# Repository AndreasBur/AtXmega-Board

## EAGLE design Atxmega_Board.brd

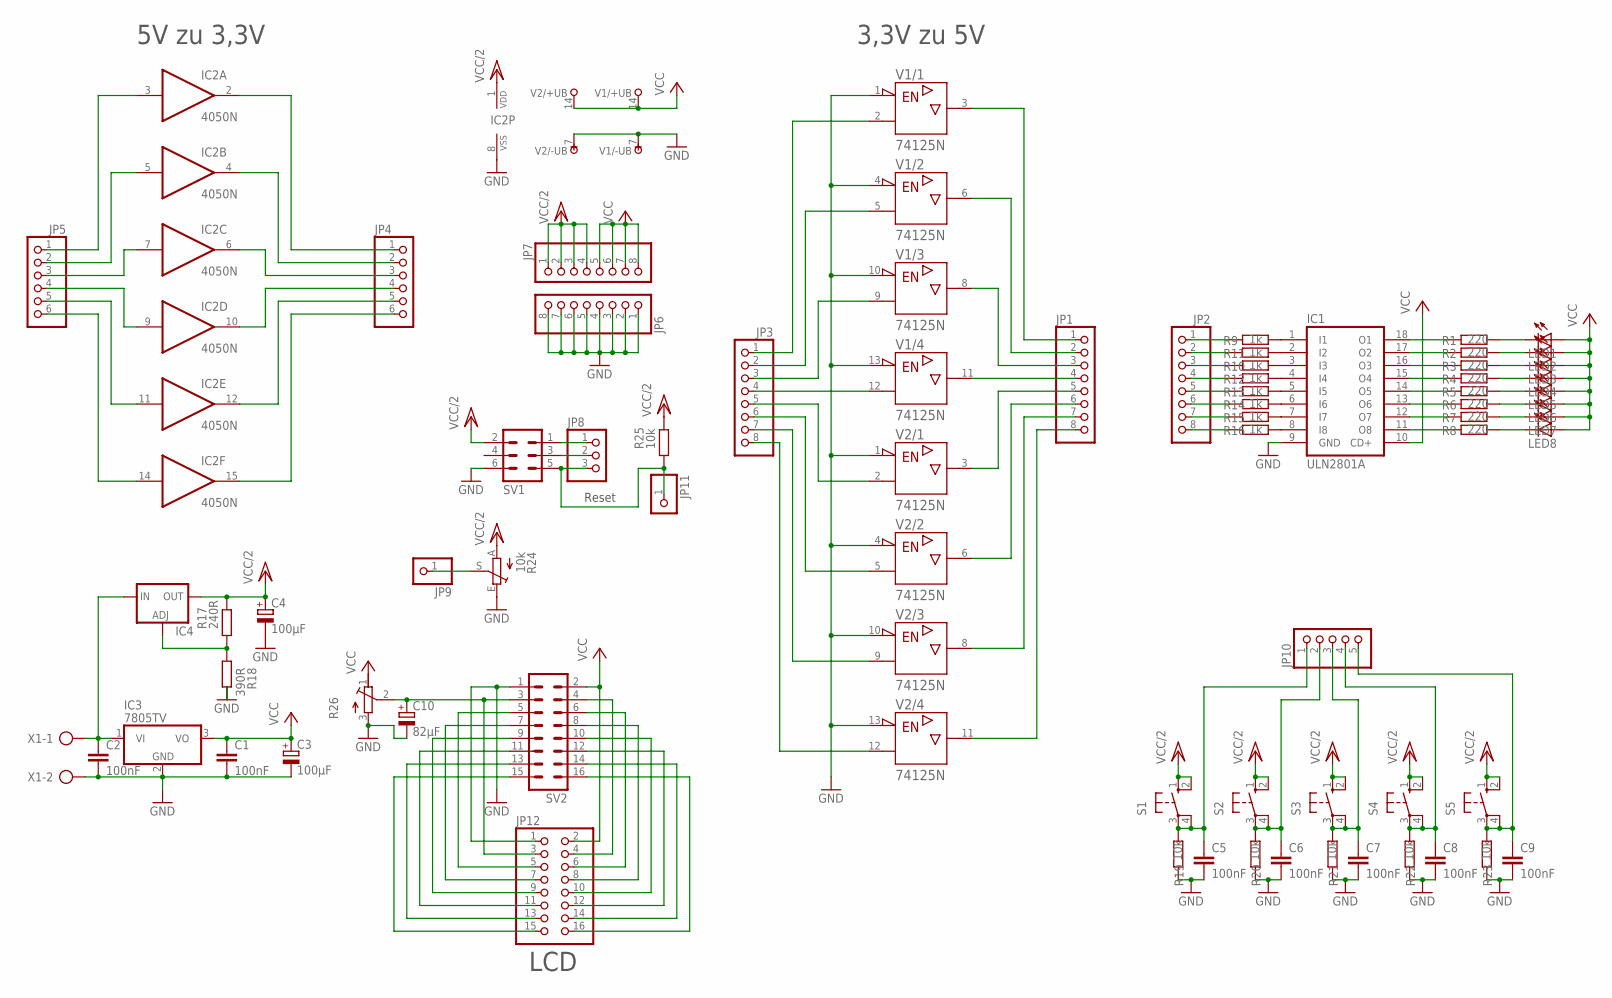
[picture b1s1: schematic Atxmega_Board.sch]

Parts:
C1, C2, C5, C6, C7, C8, C9: 100nF; C025_050-025X075
C3, C4: 100µF; E2,5-7
C10: 82µF; E2,5-7
IC1: ULN2801A; DIL18
IC2: 4050N; DIL16
IC3: 7805TV; TO220V
IC4: LM317TS; 317TS
JP1, JP2, JP3, JP6, JP7: PINHD-1X8; 1X08
JP4, JP5: PINHD-1X6; 1X06
JP8: PINHD-1X3; 1X03
JP9, JP11: PINHD-1X1; 1X01
JP10: PINHD-1X5; 1X05
JP12: PINHD-2X8; 2X08
LED1, LED2, LED3, LED4, LED5, LED6, LED7, LED8: LED5MM
R1, R2, R3, R4, R5, R6, R7, R8: 220; 0207/10
R9, R10, R11, R12, R13, R14, R15, R16: 1k; 0207/10
R17: 240R; 0207/10
R18: 390R; 0207/10
R19, R20, R21, R22, R23, R25: 10k; 0207/10
R24: 10k; ST15
R26: R-TRIMM3006P; RTRIM3006P
S1, S2, S3, S4, S5: 10-XX; B3F-10XX
SV1: ML6
SV2: ML16
V1, V2: 74125N; DIL14
X1: AK500/2

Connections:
GND: C1.2, C2.2, C3.-, C4.-, C5.2, C6.2, C7.2, C8.2, C9.2, C10.-, IC1.9 (GND), IC2.8 (VSS), IC3.2 (GND), JP6.1, JP6.2, JP6.3, JP6.4, JP6.5, JP6.6, JP6.7, JP6.8, JP12.1, R18.2, R19.1, R20.1, R21.1, R22.1, R23.1, R24.E, R26.3 (E), SV1.6, SV2.1, V1.1 (!G), V1.4 (!G), V1.7 (-UB), V1.10 (!G), V1.13 (!G), V2.1 (!G), V2.4 (!G), V2.7 (-UB), V2.10 (!G), V2.13 (!G), X1.2
unnamed: LED1.K (C), R1.2
unnamed: IC1.1 (I1), R9.2
unnamed: JP1.3, V1.8 (Y)
unnamed: JP1.2, V1.6 (Y)
unnamed: JP1.1, V1.3 (Y)
unnamed: JP1.5, V2.3 (Y)
unnamed: JP1.6, V2.6 (Y)
unnamed: JP1.7, V2.8 (Y)
unnamed: JP1.8, V2.11 (Y)
unnamed: IC1.18 (O1), R1.1
unnamed: IC1.17 (O2), R2.1
unnamed: IC1.16 (O3), R3.1
unnamed: IC1.15 (O4), R4.1
unnamed: IC1.14 (O5), R5.1
unnamed: IC1.13 (O6), R6.1
unnamed: IC1.12 (O7), R7.1
unnamed: IC1.11 (O8), R8.1
unnamed: LED2.K (C), R2.2
unnamed: LED3.K (C), R3.2
unnamed: LED4.K (C), R4.2
unnamed: LED5.K (C), R5.2
unnamed: LED6.K (C), R6.2
unnamed: LED7.K (C), R7.2
unnamed: LED8.K (C), R8.2
unnamed: JP8.1, SV1.1
unnamed: IC1.3 (I3), R10.2
unnamed: IC1.2 (I2), R11.2
unnamed: IC1.4 (I4), R12.2
unnamed: IC1.5 (I5), R13.2
unnamed: IC1.6 (I6), R14.2
unnamed: IC1.7 (I7), R15.2
unnamed: IC1.8 (I8), R16.2
unnamed: JP1.4, V1.11 (Y)
unnamed: JP2.1, R9.1
unnamed: JP2.2, R11.1
unnamed: JP2.3, R10.1
unnamed: JP2.4, R12.1
unnamed: JP2.5, R13.1
unnamed: JP2.6, R14.1
unnamed: JP2.7, R15.1
unnamed: JP2.8, R16.1
unnamed: JP3.4, V1.12 (A)
unnamed: JP3.5, V2.2 (A)
unnamed: JP3.6, V2.5 (A)
unnamed: JP3.7, V2.9 (A)
unnamed: JP3.8, V2.12 (A)
unnamed: JP3.3, V1.9 (A)
unnamed: JP3.2, V1.5 (A)
unnamed: JP3.1, V1.2 (A)
unnamed: IC2.6 (O), JP4.3
unnamed: IC2.10 (O), JP4.4
unnamed: IC2.4 (O), JP4.2
unnamed: IC2.2 (O), JP4.1
unnamed: IC2.12 (O), JP4.5
unnamed: IC2.15 (O), JP4.6
unnamed: IC2.7 (I), JP5.3
unnamed: IC2.9 (I), JP5.4
unnamed: IC2.5 (I), JP5.2
unnamed: IC2.3 (I), JP5.1
unnamed: IC2.11 (I), JP5.5
unnamed: IC2.14 (I), JP5.6
unnamed: IC4.1 (ADJ), R17.1, R18.1
unnamed: C2.1, IC3.1 (VI), IC4.3 (IN), X1.1
unnamed: C5.1, JP10.1, R19.2, S1.3, S1.4 (P1)
unnamed: C6.1, JP10.2, R20.2, S2.3, S2.4 (P1)
unnamed: C7.1, JP10.3, R21.2, S3.3, S3.4 (P1)
unnamed: C8.1, JP10.4, R22.2, S4.3, S4.4 (P1)
unnamed: C9.1, JP10.5, R23.2, S5.3, S5.4 (P1)
unnamed: JP8.2, SV1.3
unnamed: JP9.1, R24.S
unnamed: JP8.3, JP11.1, R25.1, SV1.5
unnamed: C10.+, JP12.3, R26.2 (S), SV2.3
unnamed: JP12.5, SV2.5
unnamed: JP12.7, SV2.7
unnamed: JP12.9, SV2.9
unnamed: JP12.11, SV2.11
unnamed: JP12.13, SV2.13
unnamed: JP12.15, SV2.15
unnamed: JP12.4, SV2.4
unnamed: JP12.6, SV2.6
unnamed: JP12.8, SV2.8
unnamed: JP12.10, SV2.10
unnamed: JP12.12, SV2.12
unnamed: JP12.14, SV2.14
unnamed: JP12.16, SV2.16
VCC: C1.1, C3.+, IC1.10 (CD+), IC3.3 (VO), JP7.5, JP7.6, JP7.7, JP7.8, JP12.2, LED1.A, LED2.A, LED3.A, LED4.A, LED5.A, LED6.A, LED7.A, LED8.A, R26.1 (A), SV2.2, V1.14 (+UB), V2.14 (+UB)
VCC/2: C4.+, IC2.1 (VDD), IC4.2 (OUT), JP7.1, JP7.2, JP7.3, JP7.4, R17.2, R24.A, R25.2, S1.1 (S), S1.2 (S1), S2.1 (S), S2.2 (S1), S3.1 (S), S3.2 (S1), S4.1 (S), S4.2 (S1), S5.1 (S), S5.2 (S1), SV1.2

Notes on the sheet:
Reset
3,3V zu 5V
5V zu 3,3V
LCD

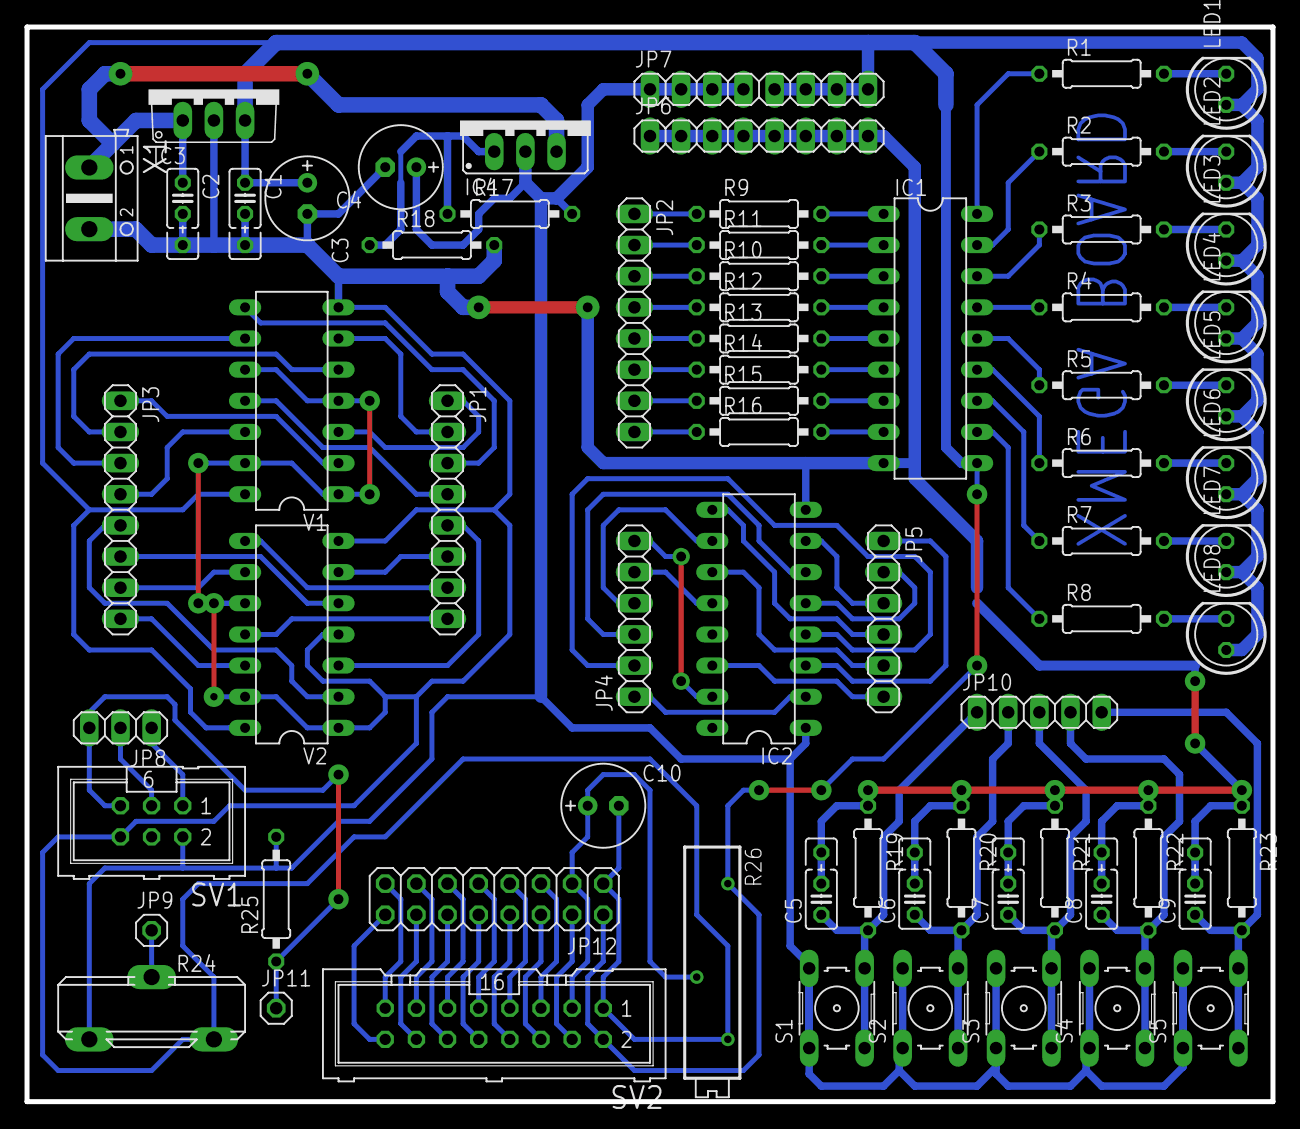
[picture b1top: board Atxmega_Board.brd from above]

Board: 2 copper layers, 101.6 x 87.6 mm, 70 parts (0 on the bottom side), 88 nets.

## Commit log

2016-11-23 added xmega board layout
